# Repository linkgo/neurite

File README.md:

[English](#) | [中文](#)

# Neurite 

A serial to MQTT bridge, an easier way to build IoT product with esp8266 Arduino.

## Contents
- [Introduction](#introduction)
  - [What Is It](#what-is-it)
  - [Who Need It](#who-need-it)
  - [Features](#features)
  - [How It Works](#how-it-works)
- [User Tutorial](#user-tutorial)
- [Developer Tutorial](#developer-tutorial)
- [Credits](#credits)
- [License](#license)

## Introduction

Neurite is named from the neural network, who takes charge of signal and information transmitting.  
In the world of IoT, the amount of smart units may be explosively large.  
Thus we are introducing Neurite, to simplify your next smart design.

### What Is It

* Neurite is an esp8266 Arduino.
* Neurite is a serial to MQTT bridge.
* Neurite is a WiFi module running corresponding firmware.
* Neurite is simply designed to be Plug-n-Play.

### Who Need It

**Neurite is great for you if:**

* You just wish to connect existing hardware to the internet and publish/subscribe data.
* You just want an easy way for all your devices to communicate with each other.

**Neurite can do a lot help if:**

* You'd like to build some MQTT ready product quickly.
* You need a hardware to integrate into your web service without pain.
* You are looking for an easier IoT solution.
* You are neat hackers. ;)

### Features

**Basic:**

* Neurite natively supports MQTT.
* Neurite publishes data from serial port to the internet.
* Neurite subscribes internet data and transfers to serial port.
* Neurite can be dynamically configured over the internet.
* Neurite is OTA enabled, for both firmware and filesystem.
* Neurite will automatically reconnect once there's network issue.

**Advanced:**

* Neurite supports all kinds of sensors and peripherals interfaced with SPI/I2C or GPIO
* Neurite benefits from 3rd party libraries thanks to esp8266 Arduino.
* Neurite is fully customizable and hackable.

### How It Works

Neurite is powered by [esp8266 Arduino](https://github.com/esp8266/Arduino), developed with [PlatformIO](http://platformio.org/).

Typical work flow:

1. Get Neurite connected to local WiFi Access Point.
2. Neurite connects to [linkgo MQTT broker](#), and subscribes to a configurable topic.
3. Neurite listens to serial port and MQTT, transparently bridges them two.

Advanced work flow besides above:

4. Neurite loops user task within a configurable interval.
5. MQTT message callbacks are registered to user logic.

## User Tutorial

1. First time setup.
    > Power on your Neurite. Switch to AP mode for the first time config, by pressing the button (over 5 seconds) until LED stops flashing.  

2. Configure Neurite to connect to your local WiFi Access Point.
    > Connect your phone, pad or laptop to `neurite-*`, navigate your browser to `linkgo.io`, choose the WiFi AP should Neurite connect to. Then Neurite will automatically reboot. 

3. Wait until Neurite gets online.
    > Neurite LED flashes fast indicates trying hard to connect according to the WiFi ssid and psk you just provided. It turns to be breathing once connected.

4. All set.
    > Now you can send/receive messages through Neurite serial port.  
    > And Neurite will automatically connect to the WiFi AP next time.

## Developer Tutorial

TODO

## Credits

[igrr](https://github.com/igrr) and all the brilliant contributors for [esp8266 Arduino](https://github.com/esp8266/Arduino).

## License

> The MIT License (MIT)
>
> Copyright (c) 2015-2018 Linkgo LLC
>
> Permission is hereby granted, free of charge, to any person obtaining a copy
> of this software and associated documentation files (the "Software"), to deal
> in the Software without restriction, including without limitation the rights
> to use, copy, modify, merge, publish, distribute, sublicense, and/or sell
> copies of the Software, and to permit persons to whom the Software is
> furnished to do so, subject to the following conditions:
>
> The above copyright notice and this permission notice shall be included in all
> copies or substantial portions of the Software.
>
> THE SOFTWARE IS PROVIDED "AS IS", WITHOUT WARRANTY OF ANY KIND, EXPRESS OR
> IMPLIED, INCLUDING BUT NOT LIMITED TO THE WARRANTIES OF MERCHANTABILITY,
> FITNESS FOR A PARTICULAR PURPOSE AND NONINFRINGEMENT. IN NO EVENT SHALL THE
> AUTHORS OR COPYRIGHT HOLDERS BE LIABLE FOR ANY CLAIM, DAMAGES OR OTHER
> LIABILITY, WHETHER IN AN ACTION OF CONTRACT, TORT OR OTHERWISE, ARISING FROM,
> OUT OF OR IN CONNECTION WITH THE SOFTWARE OR THE USE OR OTHER DEALINGS IN THE
> SOFTWARE.

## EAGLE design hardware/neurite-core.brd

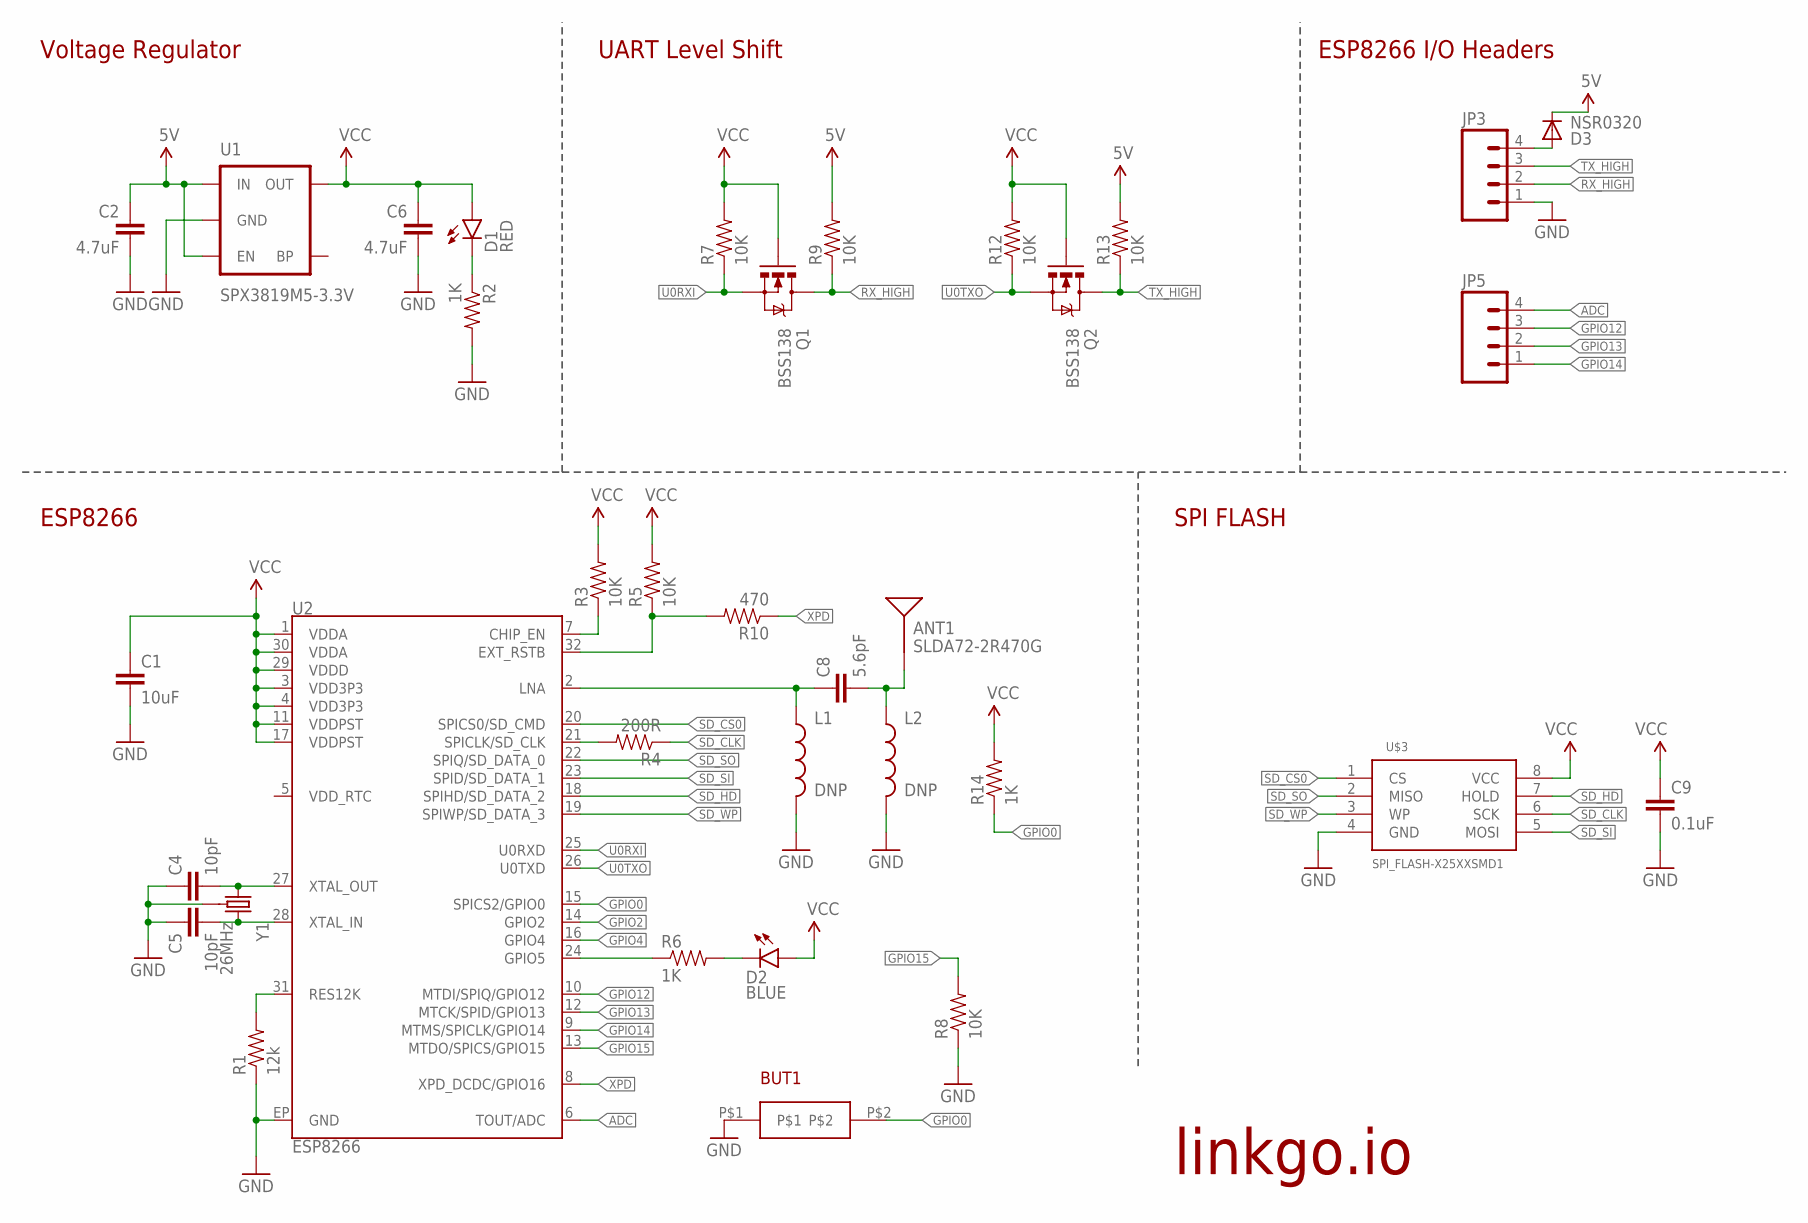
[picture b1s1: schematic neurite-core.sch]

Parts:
ANT1: SLDA72-2R470G; ANTENNA-CHIP6
BUT1: SWITCH
C1: 10uF; 0402-CAP
C2: 4.7uF; 0805
C4, C5: 10pF; 0402-CAP
C6: 4.7uF; 0603-CAP
C8: 5.6pF; 0402-CAP
C9: 0.1uF; 0402-CAP
D1: RED; LED-0603
D2: BLUE; LED-0603
D3: NSR0320; SOD-323
JP3, JP5: M04PTH; 1X04
L1, L2: DNP; C0402
Q1, Q2: BSS138; SOT23-3
R1: 12k; 0402-RES
R2, R6, R14: 1K; 0402-RES
R3, R5, R7, R8, R9, R12, R13: 10K; 0402-RES
R4: 200R; 0402-RES
R10: 470; 0402-RES
U1: SPX3819M5-3.3V; SOT23-5
U2: ESP8266; QFN32
U$3: SPI_FLASH-X25XXSMD1; SO08-EIAJ
Y1: 26MHz; CRYSTAL-SMD-3.2X2.5

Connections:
5V: C2.1, D3.1 (C), R9.2, R13.2, U1.1 (IN), U1.3 (EN)
ADC: JP5.4, U2.6 (TOUT/ADC)
CHIP_EN: R3.1, U2.7 (CHIP_EN)
GND: BUT1.P$1, C1.2, C2.2, C4.1, C5.1, C6.2, C9.2, JP3.1, L1.2, L2.2, R1.1, R2.2, R8.1, U1.2 (GND), U2.EP (GND), U$3.4 (GND), Y1.2 (GND), Y1.4 (GND)
GPIO0: BUT1.P$2, R14.1, U2.15 (SPICS2/GPIO0)
GPIO2: U2.14 (GPIO2)
GPIO4: U2.16 (GPIO4)
GPIO5: R6.1, U2.24 (GPIO5)
GPIO12: JP5.3, U2.10 (MTDI/SPIQ/GPIO12)
GPIO13: JP5.2, U2.12 (MTCK/SPID/GPIO13)
GPIO14: JP5.1, U2.9 (MTMS/SPICLK/GPIO14)
GPIO15: R8.2, U2.13 (MTDO/SPICS/GPIO15)
LNA: C8.1, L1.1, U2.2 (LNA)
unnamed: R1.2, U2.31 (RES12K)
unnamed: C5.2, U2.28 (XTAL_IN), Y1.3 (2)
unnamed: C4.2, U2.27 (XTAL_OUT), Y1.1
unnamed: D1.C, R2.1
unnamed: ANT1.1, C8.2, L2.1
unnamed: R4.2, U2.21 (SPICLK/SD_CLK)
unnamed: D3.2 (A), JP3.4
unnamed: D2.C, R6.2
RESET: R5.1, R10.2, U2.32 (EXT_RSTB)
RX_HIGH: JP3.2, Q1.3 (D), R9.1
SD_!HD!: U2.18 (SPIHD/SD_DATA_2), U$3.7 (HOLD)
SD_!WP!: U2.19 (SPIWP/SD_DATA_3), U$3.3 (WP)
SD_CLK: R4.1, U$3.6 (SCK)
SD_CS0: U2.20 (SPICS0/SD_CMD), U$3.1 (CS)
SD_SI: U2.23 (SPID/SD_DATA_1), U$3.5 (MOSI)
SD_SO: U2.22 (SPIQ/SD_DATA_0), U$3.2 (MISO)
TX_HIGH: JP3.3, Q2.3 (D), R13.1
U0RXI: Q1.2 (S), R7.1, U2.25 (U0RXD)
U0TXO: Q2.2 (S), R12.1, U2.26 (U0TXD)
VCC: C1.1, C6.1, C9.1, D1.A, D2.A, Q1.1 (G), Q2.1 (G), R3.2, R5.2, R7.2, R12.2, R14.2, U1.5 (OUT), U2.1 (VDDA), U2.3 (VDD3P3), U2.4 (VDD3P3), U2.11 (VDDPST), U2.17 (VDDPST), U2.29 (VDDD), U2.30 (VDDA), U$3.8 (VCC)
XPD: R10.1, U2.8 (XPD_DCDC/GPIO16)

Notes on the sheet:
ESP8266 I/O Headers
UART Level Shift
Voltage Regulator
ESP8266
SPI FLASH
linkgo.io

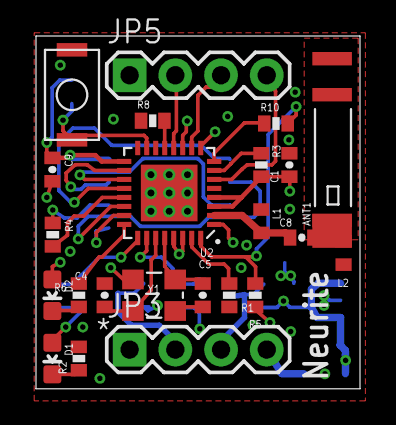
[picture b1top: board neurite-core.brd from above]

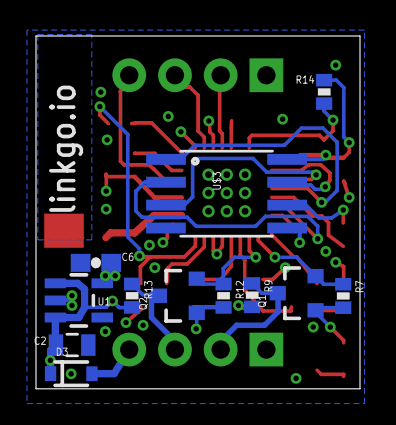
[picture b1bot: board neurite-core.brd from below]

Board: 4 copper layers, 18.0 x 19.6 mm, 35 parts (12 on the bottom side), 32 nets.

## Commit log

2015-12-11 neurite: init migrating to use esp8266 arduino
2015-12-11 add .gitignore
2015-12-11 patch: add those for arduion, which are in use
2015-12-14 basic infrastucture ready
2015-12-14 add default configs
    These shall be able to configured at runtime once device connected.
2015-12-14 add command process
2015-12-15 a bunch of updates
2015-12-15 support button press, long, short, whatever
2015-12-16 support filesystem, for config, html, css...
2015-12-16 update web server
2015-12-17 all the basic features completed: fs, ap, ota...
2015-12-18 some refines, cmds to flash firmware and spiffs
2015-12-18 cleanups, add factory reset on btn press 5s
2015-12-18 STA mode for normal work (AP disabled)
2015-12-18 fixes for config issues, add server for dev
2015-12-18 now we support mqtt push ota firmware updates!
2015-12-18 add fs readme
2015-12-18 add prebuild binaries
2015-12-18 show alive time in ms
2015-12-19 fix Serial1 issue, now we can build clean release
2015-12-20 separate dev build and release build
    Logs will be redirected into Serial1 in dev build.
2015-12-20 update prebuild binaries
2015-12-22 support PlatformIO
2015-12-22 include license
2015-12-22 add platformio custom boards for neurite
2015-12-22 minor update on config naming
2015-12-22 Travis-CI, let's do continuous integration
2015-12-22 fix travis build issue
2015-12-22 fix path
2015-12-22 fix path of boards
2015-12-22 Minor updates to enable travis-ci
2015-12-22 mv may fail on the second time, change to rm
2015-12-24 auto upload on tag in travis-ci
2015-12-24 travis-ci: fix on tags
2015-12-24 travis-ci: restore comments
2016-01-21 LED uses GPIO5 based on new hardware, tune breath
2016-01-21 update prebuild
2016-01-21 ArduinoJson compatability issue has been fixed
    https://github.com/bblanchon/ArduinoJson/commit/c57e6f3bd800a14ff5e88df73fd6efe44a18942b
2016-01-21 along with last commit, remove not needed cmd
2016-01-21 add hardware schematic and pcb layout.
2016-01-21 add interfaces for advanced development
    by the way, fix one OTA bug, that we need to truncate the payload
    buffer to be limited in "length", or the msg will be corrupted
    because PubSubClient library won't clean the buffer on each callback.
2016-01-23 some tweak with io control
2016-01-23 single io capability
2016-03-10 platformio update
2016-03-10 add mqtt command to update spiffs over otafs
2016-03-10 update default ota url
2016-03-10 update fs, merge all to html
2016-03-16 read adc, control light, servo
2016-03-17 analog write for all
2016-03-18 use user loop instead of ticker, fix a crash
    The crash occurs when long msg arrives but the buffer allocated
    in user mqtt processing routine is smaller, then wild pointer.
2016-03-18 fix a crash while ota
    we need to suspend all the possible isr to ensure ota process
2016-03-18 debug info
2016-03-23 user setup depend on connection to cloud
    This fixes the potential bugs in 3rd party modules,
    such as in servo library, servo attach will touch timer isr,
    which may then cause conflict and crash the system
    while connecting wifi.
2016-03-25 reduce trivial features for pure neurite core
2016-03-31 support dns captive portal while config wifi
    It means, we simplify wifi setup steps:
    1. connect to AP neurite-xxxxxxxx
    2. open any website in browser(will be redirected)
    3. save wifi credentials
2016-04-15 add wifiscan interface
2016-04-15 wifi scan return json format
2016-04-15 change subscribe to QOS0
    subscribe QOS1 crashes if recv msg too frequently
2016-04-15 refine json string
2016-04-15 support wifi scan when config credentials
2016-04-15 add interface to get ip
2016-04-15 only do redirecting if uri not found
2016-04-15 get location.hostname in js instead of hard code
2016-04-15 integrate light sensor, along with tweak patches
2016-04-15 customize for neurite sensor board
2016-04-15 add missing libraries of sensors, for travis
2016-04-15 simplify output
2016-04-15 integrate sensors (bme280)
2016-04-15 add bq27210, not tested yet
2016-04-15 enable bq27211 for power sensing
2016-04-15 unify topics
2016-04-15 clean up experiment stuff
2016-04-15 set wifi sta hostname as uid
2016-04-15 add debug log for server hosting
2016-04-15 remove trivial functions like servo, adc
    They are developed on separate branches.
    In fact there is one critical issue comes from Servo lib:
    Servo::attach() enables a timer, it may affect many other
    unrelated functions, such as SPIFFS.exist?
    So remove it on master branch decidedly...
2016-04-15 subscribe from chatroom
2016-04-15 remove light related stuff from master
2016-04-15 add 1.44" lcd support
2016-04-15 add ST7735 library together with GFX support
    nzmichaelh/Adafruit-ST7737-Library (support esp8266)
    adafruit/Adafruit-GFX
2016-04-15 rebase master
2016-04-15 retain checkin message in chatroom
2016-04-15 make lcd work and support bitmap logo
2016-04-15 Revert "unify topics"
    This reverts commit 2e8b0fe62f45d3bafde99bdff0fdae7d2fe4f1bb.
2016-04-15 support config via mqtt
    e.g.
    mqtt publish -h accrete.org -t /neuro/neurite-000c1632/config/ssid -m 'linkgo.io'
    mqtt publish -h accrete.org -t /neuro/neurite-000c1632/config/psk -m 'ilovelinkgo'
    mqtt publish -h accrete.org -t /neuro/neurite-000c1632/config/topic_from -m '/neuro/chatroom'
    mqtt publish -h accrete.org -t /neuro/neurite-000c1632/config/topic_to -m '/neuro/chatroom'
    mqtt publish -h accrete.org -t /neuro/neurite-000c1632/reboot -m "1"
2016-04-15 rebase master and revert topic unify manually
2016-04-16 patch: PubSubClient: increase msg size to 256
2016-04-16 sensor: assemble json format data
2016-04-16 sensor: simplify json string
2016-04-16 update wifi connection web
    1.integrated with semantic ui submodule.
    2.use dropdown to select SSID.
    3.offer scan button and show status.
2016-04-16 update fs make
    1.add index.html in fs/src
    2.use script to make fs including index.html
2016-04-17 refine wifi connection web
    1.display button inline-block
2016-04-18 apply fonts and refine charset for page loading
    1. make use of base64 to embed inline fonts.
    $ base64 quicksand-v5-latin-regular.woff2 > base64.txt
    2. add charset to avoid sluggish page reload.
2016-04-19 only keep .ttf fonts, remove woff/woff2, speed up
2016-04-19 try to minify html if possible
2016-04-20 dns: only capture linkgo.io
2016-04-20 html: submit ssid/psk only if ssid is valid
2016-04-20 check wifi status while keep trying mqtt conn
2016-04-23 separate application logic
2016-04-23 move json buf to local, discard as quickly as possible
2016-04-23 refactor all config related json stuffs
    An important update that discards obsoleted ugly config code.
2016-05-23 hardware: fix silk screen
2016-05-24 use mqtt cluster
2016-05-25 stop network monitor on restarting state machine
    This commit avoid the state machine from being restarted in a deadly
    fast loop if the new connection is not established quickly enough
    (>100ms, ticker_mon interval).
2016-05-30 enable smooth servo
2016-05-30 removed unused stuff other servo
2016-05-30 apply new code arch for servo
2016-05-30 set default topic in config.json
2016-06-03 analog data sampling, used as a knob
2016-06-03 remove unused stuff
2016-06-13 get topic_to from storage
2016-06-14 support powersave feature for sensor boards
2016-06-14 sensor: enable one shot mode
    We may only need to sample the sensor data and upload once.
2016-06-14 fix issues on old sensor branch due to rebasing
2016-06-14 fix a config unconsistent bug
2016-06-14 another rebase issue, sensor led is 13
2016-06-15 disable oneshot mode by default, for dev
2016-06-15 fix a config unconsistent bug, resolve conflict
    Conflicts:
    src/neurite.ino
2016-06-18 add patch to enable timer in both us and ms
2016-06-19 test timer in us
2016-06-21 tune to nearly 8khz
2016-06-21 try hw timer, only *can* play
2016-06-24 add breadboard and pcb image
2016-06-24 update image in README
2016-06-24 fit image
2016-06-24 update image
2016-07-06 patch: rebase upstream
2016-09-23 use linkgo.io as mqtt server
2016-09-23 use linkgo.io mqtt server, default to production
2016-09-23 update patch
2016-09-26 config server ssid value should be specified
    Without this commit, we cannot connect neurite to ssid which has
    uppercase letter in its name.
    ref: https://github.com/Semantic-Org/Semantic-UI-Docs/pull/145
2016-09-26 use submit form, redirecting to show response
2016-09-26 add grove led bar
2016-09-26 apply led bar on neurite user logic
2017-07-18 accept io control instead of bounded to bbb
2017-07-18 bbb controlled light
2017-09-28 use custom boards_dir
2018-01-15 update for travis and pio upgrading
2018-09-05 update platform, use oss
2018-09-05 support st7735 1.44" lcd
2018-09-05 add mqtt sniffer on lcd
2018-09-05 kill log warnings
2018-09-05 state ip address on checkin
2018-09-05 for egg pain counter ;P

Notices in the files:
parts and their libraries:
SparkFun-Capacitors: Licensing: Creative Commons ShareAlike 4.0 International - https://creativecommons.org/licenses/by-sa/4.0
